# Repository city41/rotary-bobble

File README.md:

# Rotary Bobble

A ROM hack, and matching controller, to add rotary controls to the Neo Geo game Puzzle Bobble

https://github.com/city41/rotary-bobble/assets/141159/24a6326e-b90c-4391-a242-a1e90e2c0111

## Status

### ROM Hack

The ROM hack is complete. It...

- gives rotary controls to all gameplay
- rotary input on high score name entry screen
- how to play screen has a spinner instead of a joystick
- each player can hold start for about 1.5 seconds to toggle between joystick and rotary controls. Useful if say playing a two player game and only have one rotary controller.

The complete patch is at `src/patches/rotary-bobble.json`

### Controller

I have built a rough, but working, prototype using an Arduino Nano.

It uses transistors to control RLDU, B, C and D. It has normal push buttons for A, Select, Start.

I also had a prototype using a Raspberry Pi Pico, but always had a little bit of noise in the Pico's analog readings, causing a bit of jitter during gameplay. The Nano has no jitter and provides perfect controls.

For more info, check the `src/pico` and `src/arduino` folders.

## IPS Patches

IPS patches are available in [releases](https://github.com/city41/rotary-bobble/releases)

1. unzip pbobblen.zip
2. patch `d96-02.c5` with `pbobblen.d96-02.c5.ips` using an IPS patcher
3. patch `d96-03.c6` with `pbobblen.d96-03.c6.ips` using an IPS patcher
4. patch `d96-07.ep1` with `pbobblen.d96-07.ep1.ips` using an IPS patcher
5. Make sure the three patched files keep the original name of the file they patched (overwrite it)
6. zip the files back up into pbobblen.zip

NOTE: MAME will notice the ROM is different and not launch it from the UI. You must launch it from the command line if using MAME

## Still To Do

- Controller

  - [x] build a working prototype
  - [x] circuit can likely be improved, just winged it...
  - [x] resolve the potentiometer noise issue, possibly with an LM4040?
  - [ ] Simple input mode to handle things like NeoSD's menu
  - [x] Figure out a good power solution for the Arduino
  - [ ] Instructions on how to create a controller

- ROM Hack
  - [x] single player rotary controls during main gameplay
  - [x] High score entry using rotary controls
  - [x] Allow player two to use rotary controls during a single player game (ie start a game with p2 instead of p1)
  - [x] Rotary controls for both players during a two player match (versus)
  - [x] Add a tagline to the title screen to indicate this is the rotary version
  - [x] Allow toggling rotary by holding start for a couple seconds
  - [x] Change the how to play to show rotary controls
  - maybe a website that easily allows applying the hack?

## How to hack on this

### clownassembler

The 68k assember, clownassembler, was copied into `clownassembler/` from https://github.com/Clownacy/clownassembler,
it needs to be built with `cd clownassembler && make`. This is needed for creating patches.

## To patch

only tested on x64 Ubuntu 22. You will need a recent version of Node, I am using 18.18.2

Set the env variable `MAME_ROM_DIR` to where you store your roms for MAME.

- `yarn install`
- copy an untouched `pbobblen.zip`, that is intended for MAME, into the root directory of the repo
  - all zips are in gitignore, so the rom won't end up in the repo
- run `ts-node src/patchRom/main.ts src/patches/rotary-bobble.json`

`rotary-bobble.json` is the main patch, and applies all changes. The patches in `patches/individual` can be applied instead to just do parts. They should be self explanatory from the file name and the description at the top of each patch.

Once patched, it will run in MAME if you start it on the command line. You can also run `yarn to-neosd` to create a .neo file. This requires [neosdconv](https://github.com/city41/neosdconv). I would prefer to use TerraOnion's NeoBuilder, but I've not gotten it to work properly.

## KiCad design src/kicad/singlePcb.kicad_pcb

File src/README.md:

# Src directories

## lua

These are MAME Lua scripts. For more info, check out [ngDebugScripts repo](https://github.com/city41/ngDebugScripts)

## patches

These are the actual patches that change Puzzle Bobble's PROM. They are JSON files and should be pretty self explanatory.

## patchRom

A TypeScript app that can take in the patch json files and do the actual patching of the p and c roms

`ts-node src/patchRom/main.ts <patch-1.json> <patch2-json> ...`

## pico

A python program that is ran on a Pico W with the controller prototype. This program translates the current value of the potentiometer and feeds that into the ROM hack via the Neo's controller port

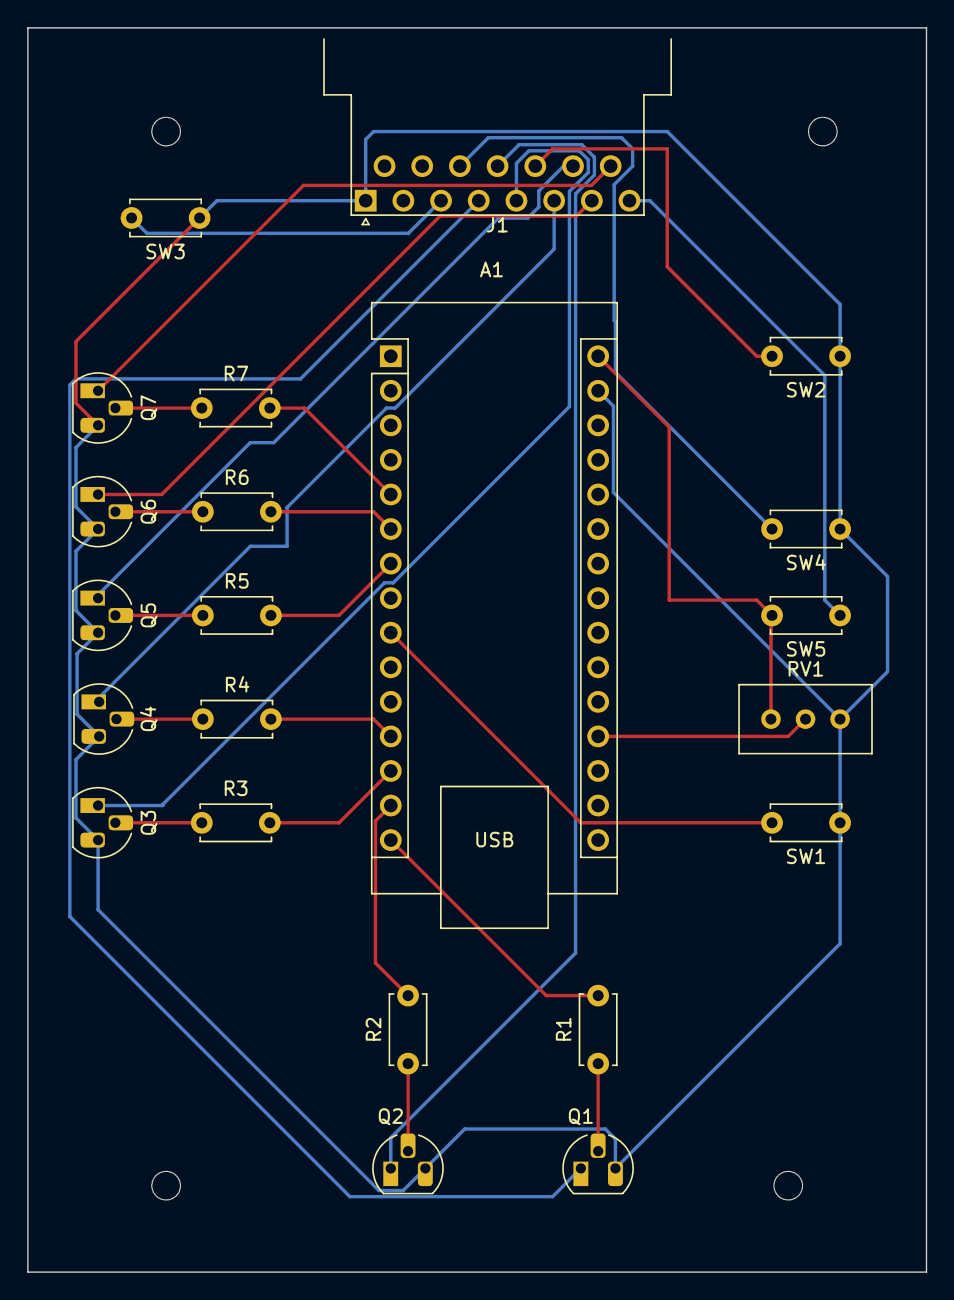
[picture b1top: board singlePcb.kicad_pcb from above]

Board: 2 copper layers, 66.0 x 91.4 mm, 26 parts (0 on the bottom side), 29 nets.

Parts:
 : MountingHole_2.1mm
 #2,  #3,  #4: MountingHole_2.1mm
A1: Arduino Nano; Arduino_Nano
J1: DA15_Receptacle; DSUB-15_Female_Horizontal_P2.77x2.54mm_EdgePinOffset9.40mm
Q1, Q2, Q3, Q4, Q5, Q6, Q7: 2N2222; TO-92_HandSolder
R1, R2, R3, R4, R5, R6, R7: 10k; C_Disc_D5.0mm_W2.5mm_P5.00mm
RV1: 10k pot; Potentiometer_Bourns_3296W_Vertical
SW1: Simple input toggle; C_Disc_D5.0mm_W2.5mm_P5.00mm
SW2: A button; C_Disc_D5.0mm_W2.5mm_P5.00mm
SW3: Select button; C_Disc_D5.0mm_W2.5mm_P5.00mm
SW4: Start button; C_Disc_D5.0mm_W2.5mm_P5.00mm
SW5: Power; C_Disc_D5.0mm_W2.5mm_P5.00mm

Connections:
GND: A1.29 (GND), J1.1, Q1.3 (C), Q2.3 (C), Q3.3 (C), Q4.3 (C), Q5.3 (C), Q6.3 (C), Q7.3 (C), RV1.1, SW1.1 (A), SW2.1 (A), SW3.1 (A), SW4.1 (A)
unnamed: A1.19 (A0), RV1.2
unnamed: A1.5 (D2), R7.2
unnamed: A1.6 (D3), R6.2
unnamed: A1.7 (D4), R5.2
unnamed: A1.9 (D6), SW1.2 (B)
unnamed: A1.12 (D9), R4.2
unnamed: A1.13 (D10), R3.2
unnamed: A1.14 (D11), R2.2
unnamed: A1.15 (D12), R1.2
unnamed: A1.30 (VIN), RV1.3, SW5.2 (B)
unnamed: J1.12, Q2.1 (E)
unnamed: J1.13, SW2.2 (B)
unnamed: J1.14, Q5.1 (E)
unnamed: J1.15, Q7.1 (E)
unnamed: J1.11 (P111), SW4.2 (B)
unnamed: Q1.2 (B), R1.1
unnamed: J1.4, Q1.1 (E)
unnamed: Q2.2 (B), R2.1
unnamed: Q3.2 (B), R3.1
unnamed: J1.5, Q3.1 (E)
unnamed: Q4.2 (B), R4.1
unnamed: J1.6, Q4.1 (E)
unnamed: Q5.2 (B), R5.1
unnamed: Q6.2 (B), R6.1
unnamed: J1.7, Q6.1 (E)
unnamed: Q7.2 (B), R7.1
unnamed: J1.8, SW5.1 (A)
unnamed: J1.3, SW3.2 (B)

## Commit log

2023-02-05 brainstorming doc
2023-02-06 Angle findings
2023-02-06 tools/flipBytes
2023-02-06 started disassembly
2023-02-12 forceRegion.ts
2023-02-12 clownassembler
2023-02-12 README
2023-02-12 forceRegion: using asm instead of raw bytes
2023-02-12 replaceWithSubroutine
2023-02-12 general patching script
2023-02-12 Found main game input routine
2023-02-12 Found where gameplay calls input routine
2023-02-12 mainInputRoutine.txt
2023-02-13 mainInputRoute: swap in BIOS labels
2023-02-18 card still inserted
2024-01-21 decompiled setShooterAngle
2024-01-21 hardcode angle to 10
2024-01-22 patch so input translates to (-60,60) angle
2024-01-22 lua script sets max positive/negative angles
2024-01-22 README: how to patch instructions
2024-01-22 sceipts/toneosd.sh
2024-01-28 pico/main.py
2024-01-28 rotationAnimation branch
2024-01-28 First pico main.py implementation
2024-01-28 README: fleshed out better
2024-01-28 Added license
2024-01-28 removed history
2024-01-28 Removed disasm
2024-01-28 Directory cleanup
2024-01-28 src dir README
2024-01-28 7bit patch: fix description
2024-01-28 7bit patch: remove fake delta lines
2024-01-28 tsconfig: fix include path
2024-01-29 setTiles disassembly
2024-01-29 fullScale.asm
2024-01-29 findings/memoryDenies
2024-01-30 memory exploration
2024-01-30 pico/main: use step down factor to reduce jitter
2024-01-30 rotation animations: working fine when traveling left
2024-01-30 graphics: start on title screen (wip)
2024-01-30 rotation animation working in both directions
2024-01-30 Main gameplay seems to fully work now
2024-01-31 controller schematic
2024-01-31 gameplay.mp4
2024-01-31 README: added video
2024-01-31 README update
2024-01-31 Setting the input at a better time
2024-01-31 multiplyShooterSpeed and hugeInputRoutine
2024-02-01 experimenting with main_median
2024-02-01 addressResolver
2024-02-02 singlePlayerRotaryControls.json
2024-02-03 README udpdate
2024-02-03 remove graphics
2024-02-03 singlePlayerRotaryControls.json: minor touch ups
2024-02-03 singlePlayer: reuse the main game angle value
2024-02-03 singlePlayer: remove commented out line
2024-02-05 highScoreRotaryControls.json
2024-02-06 singlePlayerRotaryControls: works for p1 and p2
2024-02-06 p2 single player mode now fully working
2024-02-06 README: note versus mode is working
2024-02-06 singlePlayerRotaryControls -> gameplayRotaryControls
2024-02-06 highScoreRotaryControls: remove the set g patch
2024-02-06 highScoreRotaryControls: timer to 99
2024-02-06 patch to write version to screen at start
2024-02-07 General fix layer string routine
2024-02-07 cleanup patches
2024-02-07 hold start to toggle input mode (skeleton)
2024-02-07 Note patch memory addresses
2024-02-07 high score input: joystick or rotary
2024-02-07 gameplay: toggle betwen joystick and rotary
2024-02-08 tileRecorder.lua
2024-02-09 how to play now spinner based
2024-02-09 remove all remnants of patchProm
2024-02-09 clean up temp files
2024-02-09 how to play: better spinner graphics
2024-02-09 clean up screenshots
2024-02-09 titleScreen findings
2024-02-09 Input toggling: more robust
2024-02-09 pico/main: take the median
2024-02-09 input toggle: string fixes
2024-02-10 Combine patches into one file, fixes #11
2024-02-10 update schematic
2024-02-10 Remove assumption of my machine via MAME_ROM_DIR
2024-02-10 individual patches call out
2024-02-10 fixLayerPrinting: fix comment
2024-02-10 patches: add more comments
2024-02-11 add Arduino sketches
2024-02-11 Pico -> Arduino
2024-02-11 toggle strings, bring in by one more tile
2024-02-11 main.ino: clean up
2024-02-11 making patches, do they work?
2024-02-11 creating ips patches that look ok, need to test them
2024-02-12 ips patches
2024-02-16 Start of kicad
2024-02-16 README: remove last updated date
2024-02-16 README: toggle with start, not select
2024-02-16 README: how to play wasnt a big undertaking afterall
2024-02-17 difficulty select via rotary
2024-02-17 v1.0.1a
2024-02-17 ipsPatches: zip file
2024-02-17 patchRom: basic symbole support
2024-02-17 extract rotary routine and reuse it
2024-02-17 Num player select w rotary, fixes #16
2024-02-19 lots of progress, long way to go still
2024-02-19 layout: big swaths
2024-02-19 switched to gameplay theme, going well
2024-02-19 decent progress
2024-02-20 logo done
2024-02-20 website
2024-02-20 Create CNAME
2024-02-20 website: fix title image
2024-02-20 website: tailwind as css, not js
2024-02-20 website: lighthouse fixes
2024-02-20 website: lazy load images
2024-02-21 website: fix typo
2024-02-21 website: favicon
2024-06-26 setup ips tools for neorh
2024-06-26 website: point to neorh
